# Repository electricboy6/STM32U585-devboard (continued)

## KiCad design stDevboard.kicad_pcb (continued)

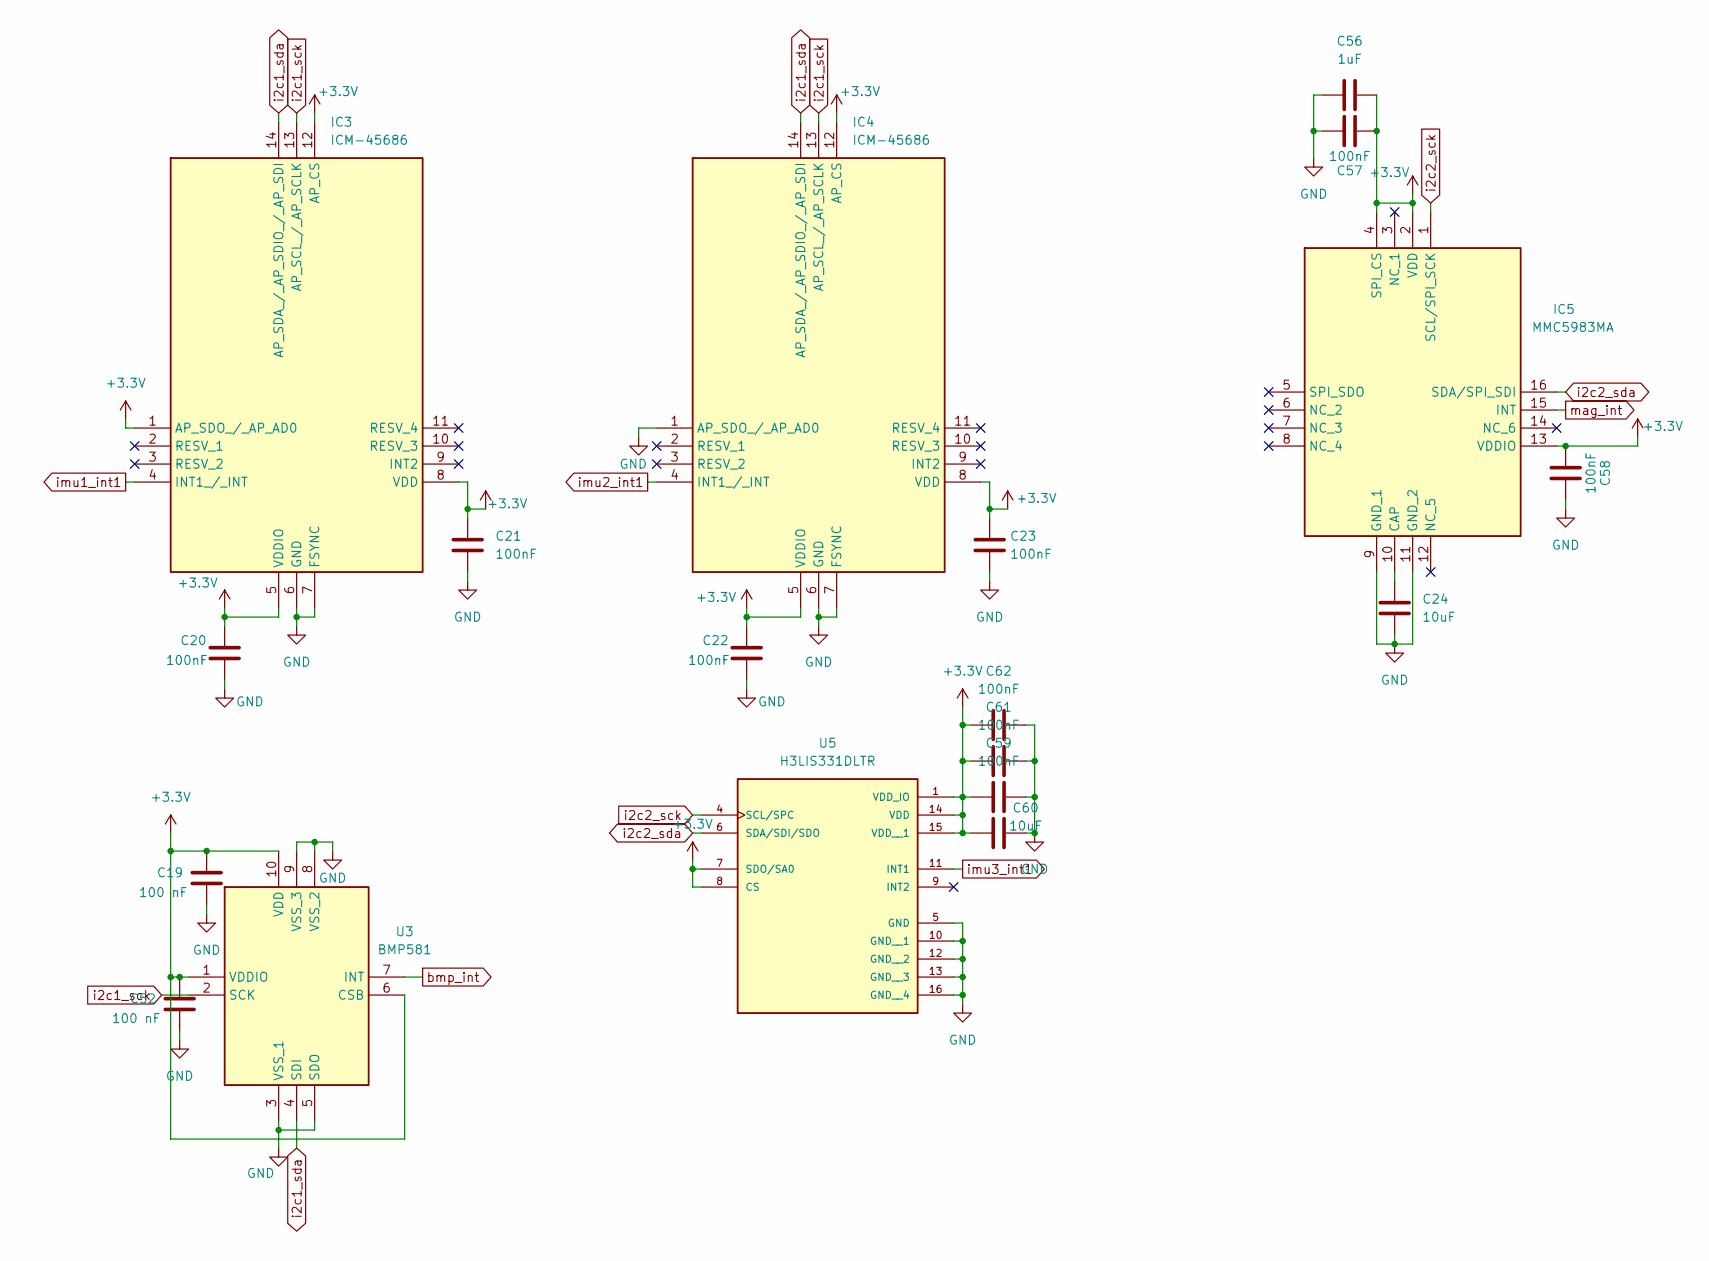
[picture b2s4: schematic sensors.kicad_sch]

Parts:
C19, C52: 100 nF; C_0402_1005Metric
C20, C21, C22, C23, C57, C58, C59, C61, C62: 100nF; C_0402_1005Metric
C24, C60: 10uF; C_0603_1608Metric
C56: 1uF; C_0603_1608Metric
IC3, IC4: ICM-45686; ICM42670P; Mouser Part Number 410-ICM-42670-P
IC5: MMC5983MA; Mouser Part Number 438-MMC5983MA
U3: BMP581; Mouser Part Number 262-BMP581
U5: H3LIS331DLTR; QFN300X300X100-16N

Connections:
+3.3V: C19.2, C20.1, C21.1, C22.1, C23.1, C52.2, C56.2, C57.2, C58.2, C59.1, C60.1, C61.1, C62.1, IC3.1 (AP_SDO_/_AP_AD0), IC3.5 (VDDIO), IC3.8 (VDD), IC3.12 (AP_CS), IC4.5 (VDDIO), IC4.8 (VDD), IC4.12 (AP_CS), IC5.2 (VDD), IC5.4 (SPI_CS), IC5.13 (VDDIO), U3.1 (VDDIO), U3.6 (CSB), U3.10 (VDD), U5.1 (VDD_IO), U5.7 (SDO/SA0), U5.8 (CS), U5.14 (VDD), U5.15 (VDD__1); also elsewhere on the board
GND: C19.1, C20.2, C21.2, C22.2, C23.2, C24.2, C52.1, C56.1, C57.1, C58.1, C59.2, C60.2, C61.2, C62.2, IC3.6 (GND), IC3.7 (FSYNC), IC4.1 (AP_SDO_/_AP_AD0), IC4.6 (GND), IC4.7 (FSYNC), IC5.9 (GND_1), IC5.11 (GND_2), U3.3 (VSS_1), U3.5 (SDO), U3.8 (VSS_2), U3.9 (VSS_3), U5.5 (GND), U5.10 (GND__1), U5.12 (GND__2), U5.13 (GND__3), U5.16 (GND__4); also elsewhere on the board
unnamed: C24.1, IC5.10 (CAP)
bmp_int: U3.7 (INT); also elsewhere on the board
i2c1_sck: IC3.13 (AP_SCL_/_AP_SCLK), IC4.13 (AP_SCL_/_AP_SCLK), U3.2 (SCK); also elsewhere on the board
i2c1_sda: IC3.14 (AP_SDA_/_AP_SDIO_/_AP_SDI), IC4.14 (AP_SDA_/_AP_SDIO_/_AP_SDI), U3.4 (SDI); also elsewhere on the board
imu1_int1: IC3.4 (INT1_/_INT); also elsewhere on the board
imu2_int1: IC4.4 (INT1_/_INT); also elsewhere on the board
imu3_int1: U5.11 (INT1); also elsewhere on the board
mag_int: IC5.15 (INT); also elsewhere on the board

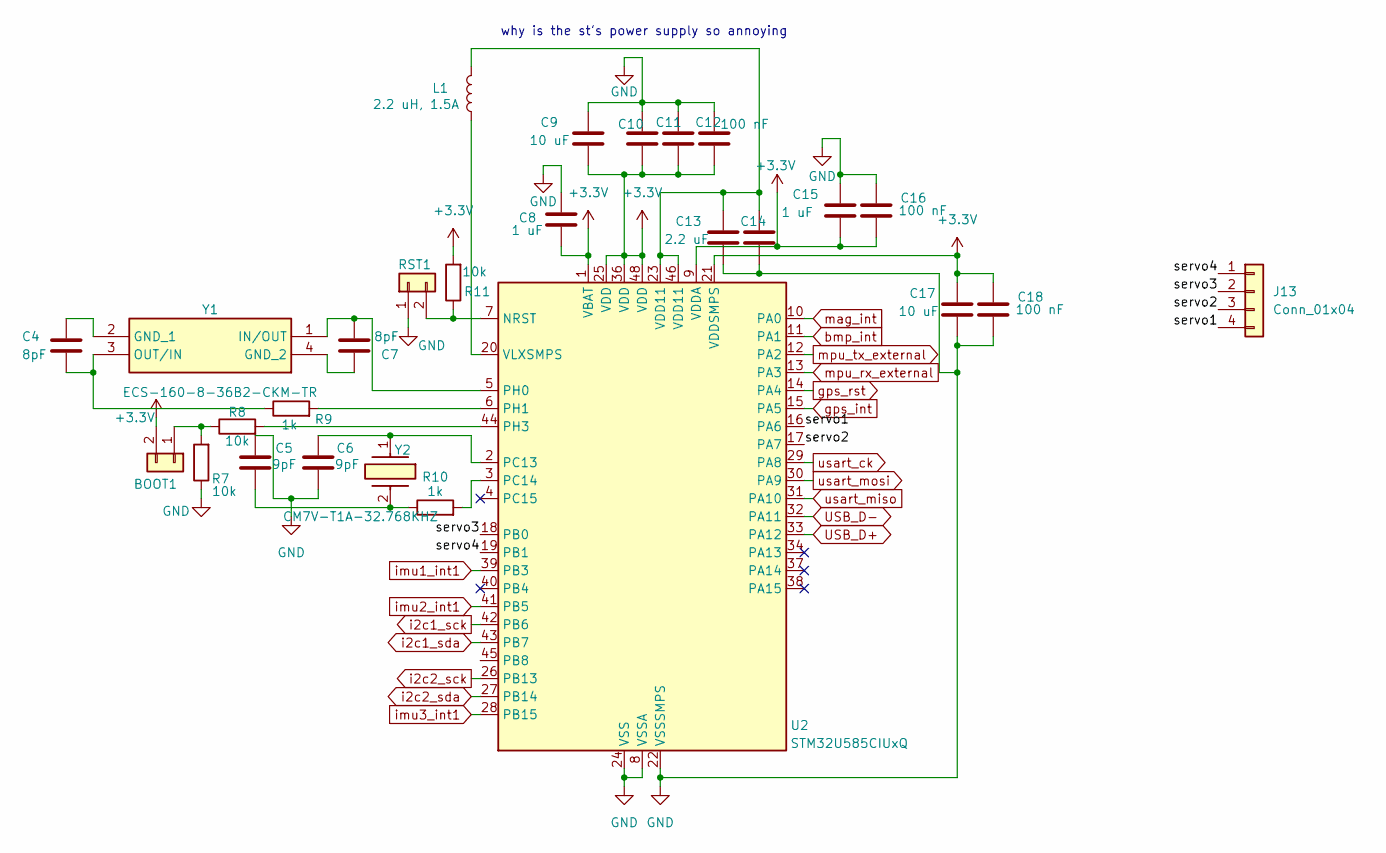
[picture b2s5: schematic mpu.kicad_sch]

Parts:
BOOT1: Conn_01x02; PinHeader_1x02_P2.54mm_Vertical
C4, C7: 8pF; C_0402_1005Metric
C5, C6: 9pF; C_0402_1005Metric
C8, C15: 1 uF; C_0603_1608Metric
C9, C17: 10 uF; C_0603_1608Metric
C10, C11, C12, C16, C18: 100 nF; C_0402_1005Metric
C13, C14: 2.2 uF; C_0603_1608Metric
J13: Conn_01x04; PinHeader_1x04_P2.54mm_Vertical
L1: 2.2 uH, 1.5A; INDC2520X120N
R7, R8, R11: 10k; R_0402_1005Metric
R9, R10: 1k; R_0402_1005Metric
RST1: Conn_01x02; PinHeader_1x02_P2.54mm_Vertical
U2: STM32U585CIUxQ; QFN-48-1EP_7x7mm_P0.5mm_EP5.6x5.6mm
Y1: ECS-160-8-36B2-CKM-TR; ECS160836B2CKMTR; Mouser Part Number 520-160-8-36B2-CKMTR
Y2: CM7V-T1A-32.768KHZ; CM7V32768TBQA020; Mouser Part Number 428-201565-MG01

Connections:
+3.3V: BOOT1.2, C8.2, C9.2, C10.2, C11.2, C12.2, C15.2, C16.2, C17.1, C18.1, R11.2, U2.1 (VBAT), U2.9 (VDDA), U2.21 (VDDSMPS), U2.25 (VDD), U2.36 (VDD), U2.48 (VDD); also elsewhere on the board
GND: C5.1, C6.2, C8.1, C9.1, C10.1, C11.1, C12.1, C13.2, C14.2, C15.1, C16.1, C17.2, C18.2, R7.1, RST1.1, U2.8 (VSSA), U2.22 (VSSSMPS), U2.24 (VSS), U2.35 (VSS), U2.47 (VSS), U2.49 (VSS); also elsewhere on the board
unnamed: BOOT1.1, R7.2, R8.1
unnamed: C5.2, R10.1, Y2.2
unnamed: C13.1, C14.1, L1.2, U2.23 (VDD11), U2.46 (VDD11)
unnamed: R11.1, RST1.2, U2.7 (NRST)
unnamed: C6.1, U2.2 (PC13), Y2.1
unnamed: R10.2, U2.3 (PC14)
unnamed: C7.1, U2.5 (PH0), Y1.1 (IN/OUT)
unnamed: R9.2, U2.6 (PH1)
unnamed: R8.2, U2.44 (PH3)
unnamed: L1.1, U2.20 (VLXSMPS)
unnamed: C4.2, Y1.2 (GND_1)
unnamed: C7.2, Y1.4 (GND_2)
unnamed: C4.1, R9.1, Y1.3 (OUT/IN)
USB_D+: U2.33 (PA12); also elsewhere on the board
USB_D-: U2.32 (PA11); also elsewhere on the board
bmp_int: U2.11 (PA1); also elsewhere on the board
gps_int: U2.15 (PA5); also elsewhere on the board
gps_rst: U2.14 (PA4); also elsewhere on the board
i2c1_sck: U2.42 (PB6); also elsewhere on the board
i2c1_sda: U2.43 (PB7); also elsewhere on the board
imu1_int1: U2.39 (PB3); also elsewhere on the board
imu2_int1: U2.41 (PB5); also elsewhere on the board
imu3_int1: U2.28 (PB15); also elsewhere on the board
mag_int: U2.10 (PA0); also elsewhere on the board
mpu_rx_external: U2.13 (PA3); also elsewhere on the board
mpu_tx_external: U2.12 (PA2); also elsewhere on the board
usart_ck: U2.29 (PA8); also elsewhere on the board
usart_miso: U2.31 (PA10); also elsewhere on the board
usart_mosi: U2.30 (PA9); also elsewhere on the board

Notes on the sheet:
why is the st's power supply so annoying

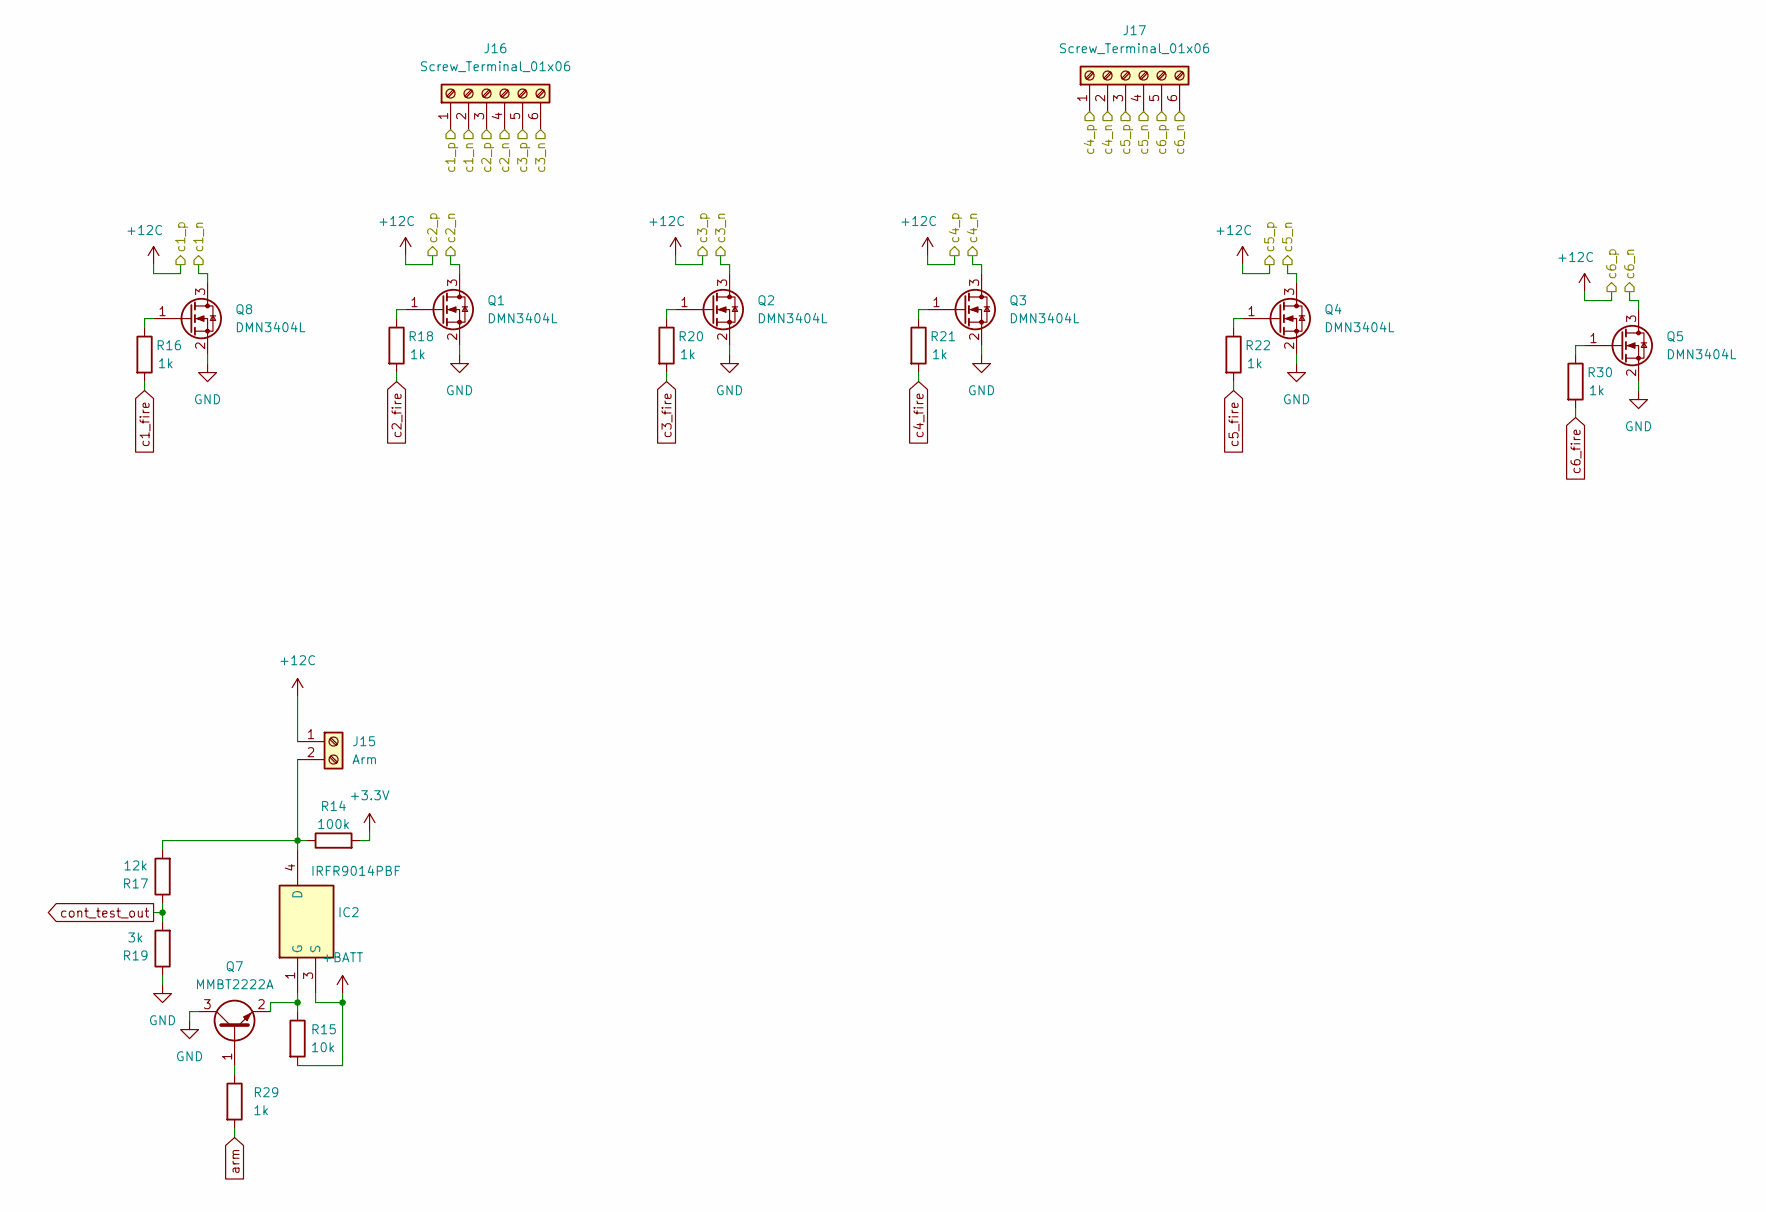
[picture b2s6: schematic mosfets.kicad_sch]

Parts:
IC2: IRFR9014PBF; TO228P990X238-3N; Mouser Part Number 844-IRFR9014PBF
J15: Arm; TerminalBlock_Xinya_XY308-2.54-2P_1x02_P2.54mm_Horizontal
J16, J17: Screw_Terminal_01x06; TerminalBlock_Xinya_XY308-2.54-6P_1x06_P2.54mm_Horizontal
Q1, Q2, Q3, Q4, Q5, Q8: DMN3404L; SOT-23
Q7: MMBT2222A; SOT-23
R14: 100k; R_0402_1005Metric
R15: 10k; R_0402_1005Metric
R16, R18, R20, R21, R22, R29, R30: 1k; R_0402_1005Metric
R17: 12k; R_0402_1005Metric
R19: 3k; R_0402_1005Metric

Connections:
+3.3V: R14.2; also elsewhere on the board
+12C: J15.1, J16.1, J16.3, J16.5, J17.1, J17.3, J17.5; also elsewhere on the board
+BATT: IC2.3 (S), R15.2; also elsewhere on the board
/mosfets/c1_n: J16.2, Q8.3 (D); also elsewhere on the board
/mosfets/c2_n: J16.4, Q1.3 (D); also elsewhere on the board
/mosfets/c3_n: J16.6, Q2.3 (D); also elsewhere on the board
/mosfets/c4_n: J17.2, Q3.3 (D); also elsewhere on the board
/mosfets/c5_n: J17.4, Q4.3 (D); also elsewhere on the board
/mosfets/c6_n: J17.6, Q5.3 (D); also elsewhere on the board
GND: Q1.2 (S), Q2.2 (S), Q3.2 (S), Q4.2 (S), Q5.2 (S), Q7.3 (C), Q8.2 (S), R19.1; also elsewhere on the board
unnamed: IC2.4 (D), J15.2, R14.1, R17.2
unnamed: IC2.1 (G), Q7.2 (E), R15.1
unnamed: Q1.1 (G), R18.1
unnamed: Q2.1 (G), R20.1
unnamed: Q3.1 (G), R21.1
unnamed: Q4.1 (G), R22.1
unnamed: Q5.1 (G), R30.1
unnamed: Q7.1 (B), R29.1
unnamed: Q8.1 (G), R16.1
arm: R29.2; also elsewhere on the board
c1_fire: R16.2; also elsewhere on the board
c2_fire: R18.2; also elsewhere on the board
c3_fire: R20.2; also elsewhere on the board
c4_fire: R21.2; also elsewhere on the board
c5_fire: R22.2; also elsewhere on the board
c6_fire: R30.2; also elsewhere on the board
cont_test_out: R17.1, R19.2; also elsewhere on the board

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
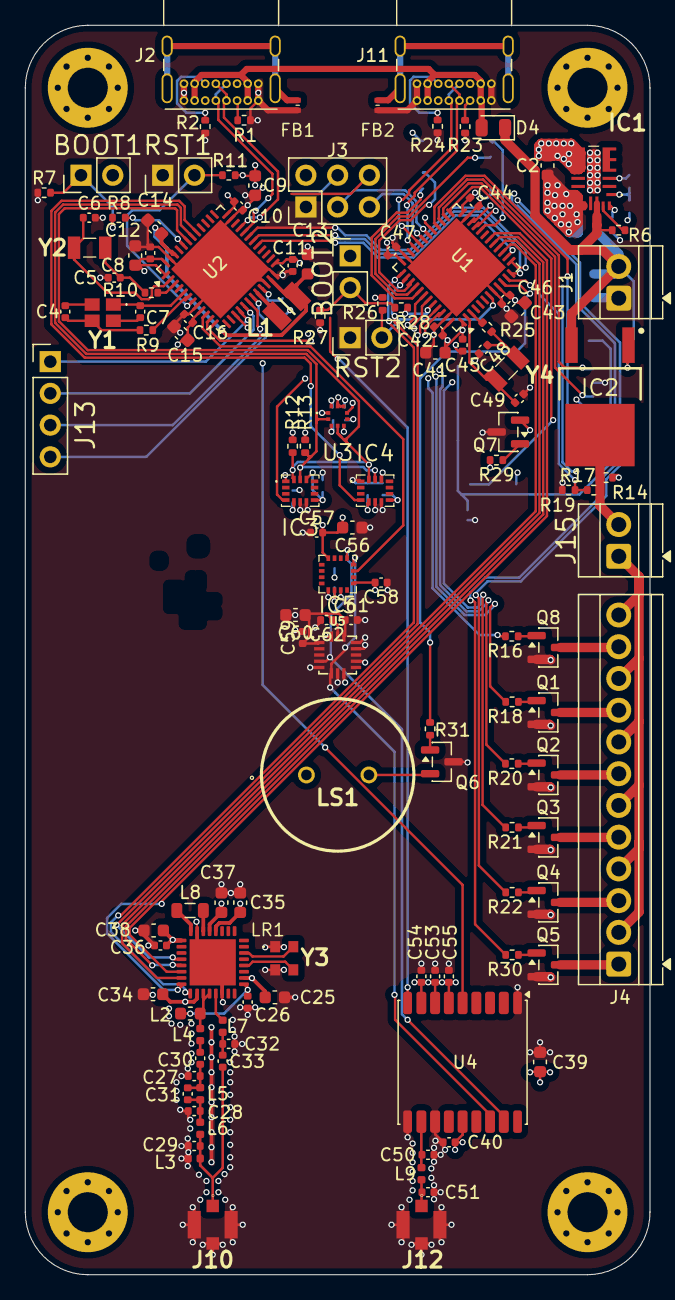
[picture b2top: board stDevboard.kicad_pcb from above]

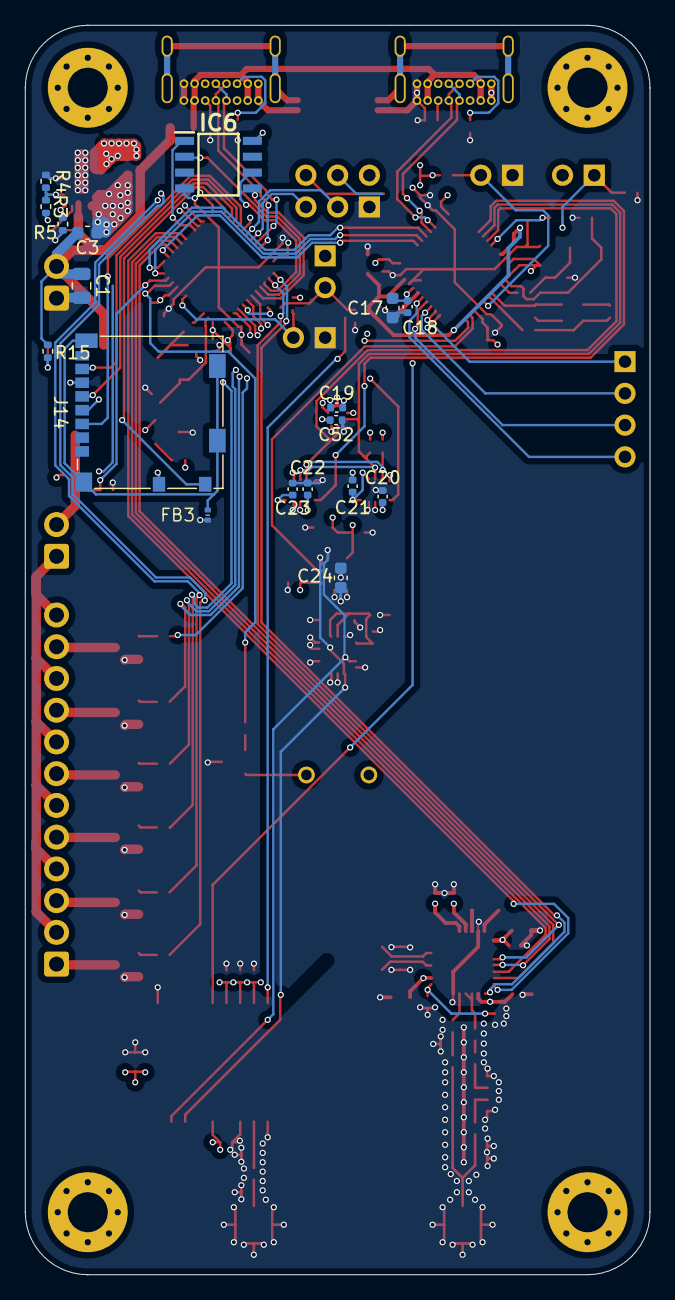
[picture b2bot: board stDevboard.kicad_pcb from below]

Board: 4 copper layers, 50.0 x 100.0 mm, 145 parts (18 on the bottom side), 116 nets.

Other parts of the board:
J4: Screw_Terminal_01x12; TerminalBlock_Xinya_XY308-2.54-12P_1x12_P2.54mm_Horizontal

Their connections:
+12C: J4.2, J4.4, J4.6, J4.8, J4.10, J4.12; also elsewhere on the board
/mosfets/c1_n: J4.11; also elsewhere on the board
/mosfets/c2_n: J4.9; also elsewhere on the board
/mosfets/c3_n: J4.7; also elsewhere on the board
/mosfets/c4_n: J4.5; also elsewhere on the board
/mosfets/c5_n: J4.3; also elsewhere on the board
/mosfets/c6_n: J4.1; also elsewhere on the board

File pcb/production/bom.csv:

Designator,Footprint,Quantity,Value,LCSC Part #
"BOOT1, BOOT2, RST1, RST2",PinHeader_1x02_P2.54mm_Vertical,4,Conn_01x02,
C1,0805,1,10uF,
"C10, C11, C12, C16, C18, C19, C52",0402,7,100 nF,
"C13, C14",0603,2,2.2 uF,
"C15, C8",0603,2,1 uF,
"C17, C9",0603,2,10 uF,
C2,0603,1,22uF,
"C20, C21, C22, C23, C36, C40, C42, C44, C45, C46, C47, C53, C54, C55",0402,14,100nF,
"C24, C3, C39, C41",0603,4,10uF,
"C25, C37",0603,2,2.2uF,
C26,0402,1,47pF,
C27,0402,1,7.5pF,
C28,0402,1,3.9pF,
"C29, C31",0402,2,1.8pF,
C30,0402,1,22pF,
C32,0402,1,2.2pF,
C33,0402,1,18pF,
"C34, C35, C43",0603,3,1uF,
C38,0603,1,4.7uF,
"C4, C7",0402,2,8pF,
"C48, C49, C5, C6",0402,4,9pF,
D4,0805,1,D_Schottky,
"FB1, FB2, FB3",NFZ15SG152SN10B,3,BLM15AX102SN1D,
IC1,MPM3606GQVZ,1,MPM3610GQV-Z,
IC2,TO228P990X238-3N,1,IRFR9014PBF,
"IC3, IC4",ICM42670P,2,ICM-45686,
IC5,MMC5983MA,1,MMC5983MA,
IC6,SOIC127P600X175-8N,1,AT25SF041B-SSHB-B,
J1,TerminalBlock_Xinya_XY308-2.54-2P_1x02_P2.54mm_Horizontal,1,battery,
"J10, J12",73412-0110,2,73412-0114,
"J11, J2",USB_C_Receptacle_GCT_USB4085,2,USB_C_Receptacle_USB2.0_16P,
J13,PinHeader_1x04_P2.54mm_Vertical,1,Conn_01x04,
J14,microSD_HC_Molex_104031-0811,1,Micro_SD_Card_Det2,
J15,TerminalBlock_Xinya_XY308-2.54-2P_1x02_P2.54mm_Horizontal,1,Arm,
J3,PinHeader_2x03_P2.54mm_Vertical,1,Conn_02x03_Top_Bottom,
J4,TerminalBlock_Xinya_XY308-2.54-12P_1x12_P2.54mm_Horizontal,1,Screw_Terminal_01x12,
L1,INDC2520X120N,1,"2.2 uH, 1.5A",
L2,0603,1,12nH,
L3,0402,1,22nH,
L4,0402,1,4.7nH,
L5,0402,1,3.9nH,
L6,0402,1,7.5nH,
L7,0402,1,24nH,
L8,0805,1,2.2uH,
LR1,LR2021,1,~,
LS1,PS1240P02BT,1,PS1240P02BT,
"Q1, Q2, Q3, Q4, Q5, Q8",SOT-23,6,DMN3404L,
Q7,SOT-23,1,MMBT2222A,
"R1, R2, R23, R24",0402,4,5.1K,
"R10, R16, R18, R20, R21, R22, R25, R29, R30, R9",0402,10,1k,
"R11, R15, R26, R27, R28, R7, R8",0402,7,10k,
"R12, R13",0402,2,2.7k,
"R14, R6",0402,2,100k,
R17,0402,1,12k,
R19,0402,1,3k,
R3,0402,1,75k,
R4,0402,1,24k,
R5,0402,1,39k,
U1,QFN-48-1EP_7x7mm_P0.5mm_EP5.6x5.6mm_ThermalVias,1,STM32U073CCUx,
U2,QFN-48-1EP_7x7mm_P0.5mm_EP5.6x5.6mm_ThermalVias,1,STM32U585CIUxQ,
U3,BMP581,1,BMP581,
U4,ublox_MAX,1,MAX-M10S,
Y1,ECS160836B2CKMTR,1,ECS-160-8-36B2-CKM-TR,
"Y2, Y4",CM7V32768TBQA020,2,CM7V-T1A-32.768KHZ,
Y3,ECSTXO25CSMV320AMTR,1,ECS-TXO-25CSMV-320-AM-TR,

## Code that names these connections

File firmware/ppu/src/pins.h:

#pragma once

#include <Arduino.h>
#include <SPI.h>

// analog reference voltage
const float ANALOG_REF = 3.3;
// number of adc levels
const float ANALOG_STEPS = (1 << 12) - 1; // configured for 12 bit adc read

namespace pins {
    // vbat sense analog pin
    const byte vbat         = PB1;

    // continuity test result analog pin
    const byte cont_test    = PA1;
    const byte arm          = PA8;
    const byte c0_fire      = PB6;
    const byte c1_fire      = PB7;
    const byte c2_fire      = PB8;
    const byte c3_fire      = PB9;
    const byte c4_fire      = PB10;
    const byte c5_fire      = PB11;

    const byte telem_cs     = PB0;
    const byte telem_busy   = PA14;
    const byte telem_rst    = PA15;

    const byte piezo        = PA0;

    const byte flash_cs     = PB2;


    // mpu
    inline HardwareSerial interconnectSerial(PA10, PA9);

    // broken out on header
    inline HardwareSerial debugSerial(PA3, PA2);

    // flash spi
    inline SPIClass flash(PB5, PB4, PB3);

    // sd spi
    //inline SPIClass sd(PB15, PB14, PB13, PB12);

    // telemetry spi
    inline SPIClass telem(PA7, PA6, PA5);

    // init all serials and spis
    void init();
}

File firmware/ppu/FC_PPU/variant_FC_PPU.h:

#ifndef _VARIANT_ARDUINO_STM32_
#define _VARIANT_ARDUINO_STM32_
#endif

#ifdef __cplusplus
extern "C" {
#endif

// pin defs
#define PA0  10
#define PA1  11
#define PA2  12
#define PA3  13
#define PA4  14
#define PA5  15
#define PA6  16
#define PA7  17
#define PA8  29
#define PA9  30
#define PA10 31
#define PA11 32
#define PA12 33
#define PA13 34
#define PA14 37
#define PA15 38
#define PB0  18
#define PB1  19
#define PB2  20
#define PB3  39
#define PB4  40
#define PB5  41
#define PB6  42
#define PB7  43
#define PB8  45
#define PB9  46
#define PB10 21
#define PB11 22
#define PB12 25
#define PB13 26
#define PB14 27
#define PB15 28


#define NUM_DIGITAL_PINS 32
#define NUM_ANALOG_INPUTS 2

// Use TIM6/TIM7 when possible as servo and tone don't need GPIO output pin
#define TIMER_TONE TIM6
#define TIMER_SERVO TIM7

#define SERIAL_UART_INSTANCE 1

#define PIN_SERIAL_RX 31
#define PIN_SERIAL_TX 30

// sd defs
#define SDCARD_MOSI_PIN PB15
#define SDCARD_MISO_PIN PB14
#define SDCARD_SCK_PIN PB13
#define SDCARD_SS_PIN PB12

// hal modules
#define HAL_I2C_MODULE_DISABLED

#ifdef __cplusplus
}
#endif

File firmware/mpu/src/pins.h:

#pragma once

#include <Arduino.h>
#include <Wire.h>

namespace pins {
    const int mag_int = PA0;
    const int bmp_int = PA1;
    const int gps_rst = PA4;
    const int gps_int = PA5;
    const int imu1_int = PB3;
    const int imu2_int = PB5;
    const int accel_int = PB15;

    // +X
    const int servo1 = PA6;
    // +Y
    const int servo2 = PA7;
    // -X
    const int servo3 = PB0;
    // -Y
    const int servo4 = PB1;

    // ppu
    inline HardwareSerial interconnectSerial(PA10, PA9);

    // broken out on header
    inline HardwareSerial debugSerial(PA3, PA2);

    // imus, baro
    inline TwoWire i2cFast(PB7, PB6);

    // mag, gps, accel
    inline TwoWire i2cSlow(PB14, PB13);

    // init all serials and i2cs
    void init();
}

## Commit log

2025-10-13 initial
2025-10-13 worked on schematic
2025-10-14 worked some more on schematic, also figured out more of oscillator stuff and boot button
2025-10-14 Create JOURNAL.md since it wasn't remade when I reuploaded the repo
2025-10-23 worked on a ton of stuff, see journal for details
2025-10-23 added libs
2025-10-23 added new schematic
2025-10-26 everything I did while on vacation - initial schematic finished, footprints mostly assigned, and pcb layout started
2025-10-27 pcb coming along, schematic way more done - I now have a lot more respect for hardware people than I did earlier
2025-11-10 tons of work, see journal for details
2025-11-26 oops forgot to commit - looks like I worked on the lr2021's symbol and the schematic - see journal for details on what I did
2025-11-30 tons of progress on schematic and pcb - see journal for details
2025-11-30 added mounting holes, moved power stuff, routed secondary micro, moved sensors
2025-12-02 worked mainly on pcb
2025-12-02 basically just decoupling capacitors that I forgot
2025-12-04 worked on adding mosfet stuff, last of the major signal traces routed
2025-12-07 added in the flash chip and micro sd card, rerouted some stuff, looking real nice rn - still need to finish rf, pyros, and add in the piezo
2025-12-08 added piezo buzzer, rf hopefully finished! just need to send to mpk for check now
2025-12-10 mosfet schematic done I hope
2025-12-10 mosfet schematic should be finalized
2025-12-10 placed mosfet stuff, probably all that's left is add pull resistors on the nfets and finish routing the fets
2025-12-11 idk what I did but it wasn't saved
2025-12-13 almost done routing! getting pretty close to done now
2025-12-13 routing done! silkscreen is probably good enough for now
2025-12-14 stiching and fencing vias, fixed via diameters
2025-12-15 added decoupling caps, added high g accel - about to redo basically all of the pin allocations on the mpu so I can have a high speed and low speed i2c
2025-12-19 schematic updated - need to redo the layout now
2025-12-19 started redoing layout for new pinout
2025-12-19 finished the reroute - just need to redo silkscreen and verify everything
2025-12-19 restructured repo
2025-12-19 removed useless stuff
2025-12-20 rerouted oscillator stuff - still need to finish i2c routing, also started a platformio board definition
2025-12-20 missing file from previous commit
2025-12-20 fixed some stuff with board def
2025-12-20 reroute done! except for the gps which I'm currently verifying my implementation on
2025-12-20 board def hopefully done, mpu test firmware written
2025-12-21 added models for some things, fixed micro sd impl and a bunch of other stuff - pcb currently probably ready for production
2025-12-21 start of ppu firmware
2025-12-21 started making bom - changed some stuff for compatibility with it
2025-12-22 lots of work on ppu firmware, especially relating to flash - also corrected some schematic errors (haven't gotten around to updating pcb yet)
2025-12-22 updated pcb from schematic changes, also added some length tuning because why not
2025-12-22 flash driver done, started littlefs integration - only the header and the hal functions done so far, still need to write the wrappers
2025-12-23 mainly worked on bom (still just on google sheets), but while doing so fixed some issues and redid some component selection
2025-12-23 littlefs integration done! there's so much boilerplate it was so annoying
2025-12-23 initial ppu testing firmware done
2025-12-23 added bom
2025-12-23 oops had extra rows in bom, fixed now
2025-12-26 reorganized schematic, started to add a readme (not really though), also pcb updated
2025-12-26 added camera high side switching
2025-12-26 modified gps for an active antenna
2025-12-26 fixed up silkscreen a bit
2025-12-27 actually added a name to readme!
2025-12-27 fixed micro sd pullups
2025-12-27 added a license
2025-12-27 mostly wrote the readme, still need pictures
2025-12-27 yay added 3d models for some missing parts
2025-12-29 fixed vr_pa trace impedance (thanks mpk)
2025-12-29 YAY pictures in readme, just need to update BoM and submit!
2025-12-31 bom finalized
2025-12-31 added gerbers
2025-12-31 added bom to readme, fab options
2026-01-01 updated bom for new flash chip
2026-01-02 added silkscreen art and credits
2026-01-03 updated gerbers, missing files
2026-01-04 hopefully clarified bom
2026-01-04 made bom more readable again
2026-01-11 final gerber that was produced
2026-01-24 last open source commit - moving to closed source firmware development now
2026-01-24 update readme with notice and remove reviewer note
2026-01-24 add a section for any issues found
    oops those 22uf caps are rated for 6.3v and they should be more of 25v rated oh well it doesn't really matter
